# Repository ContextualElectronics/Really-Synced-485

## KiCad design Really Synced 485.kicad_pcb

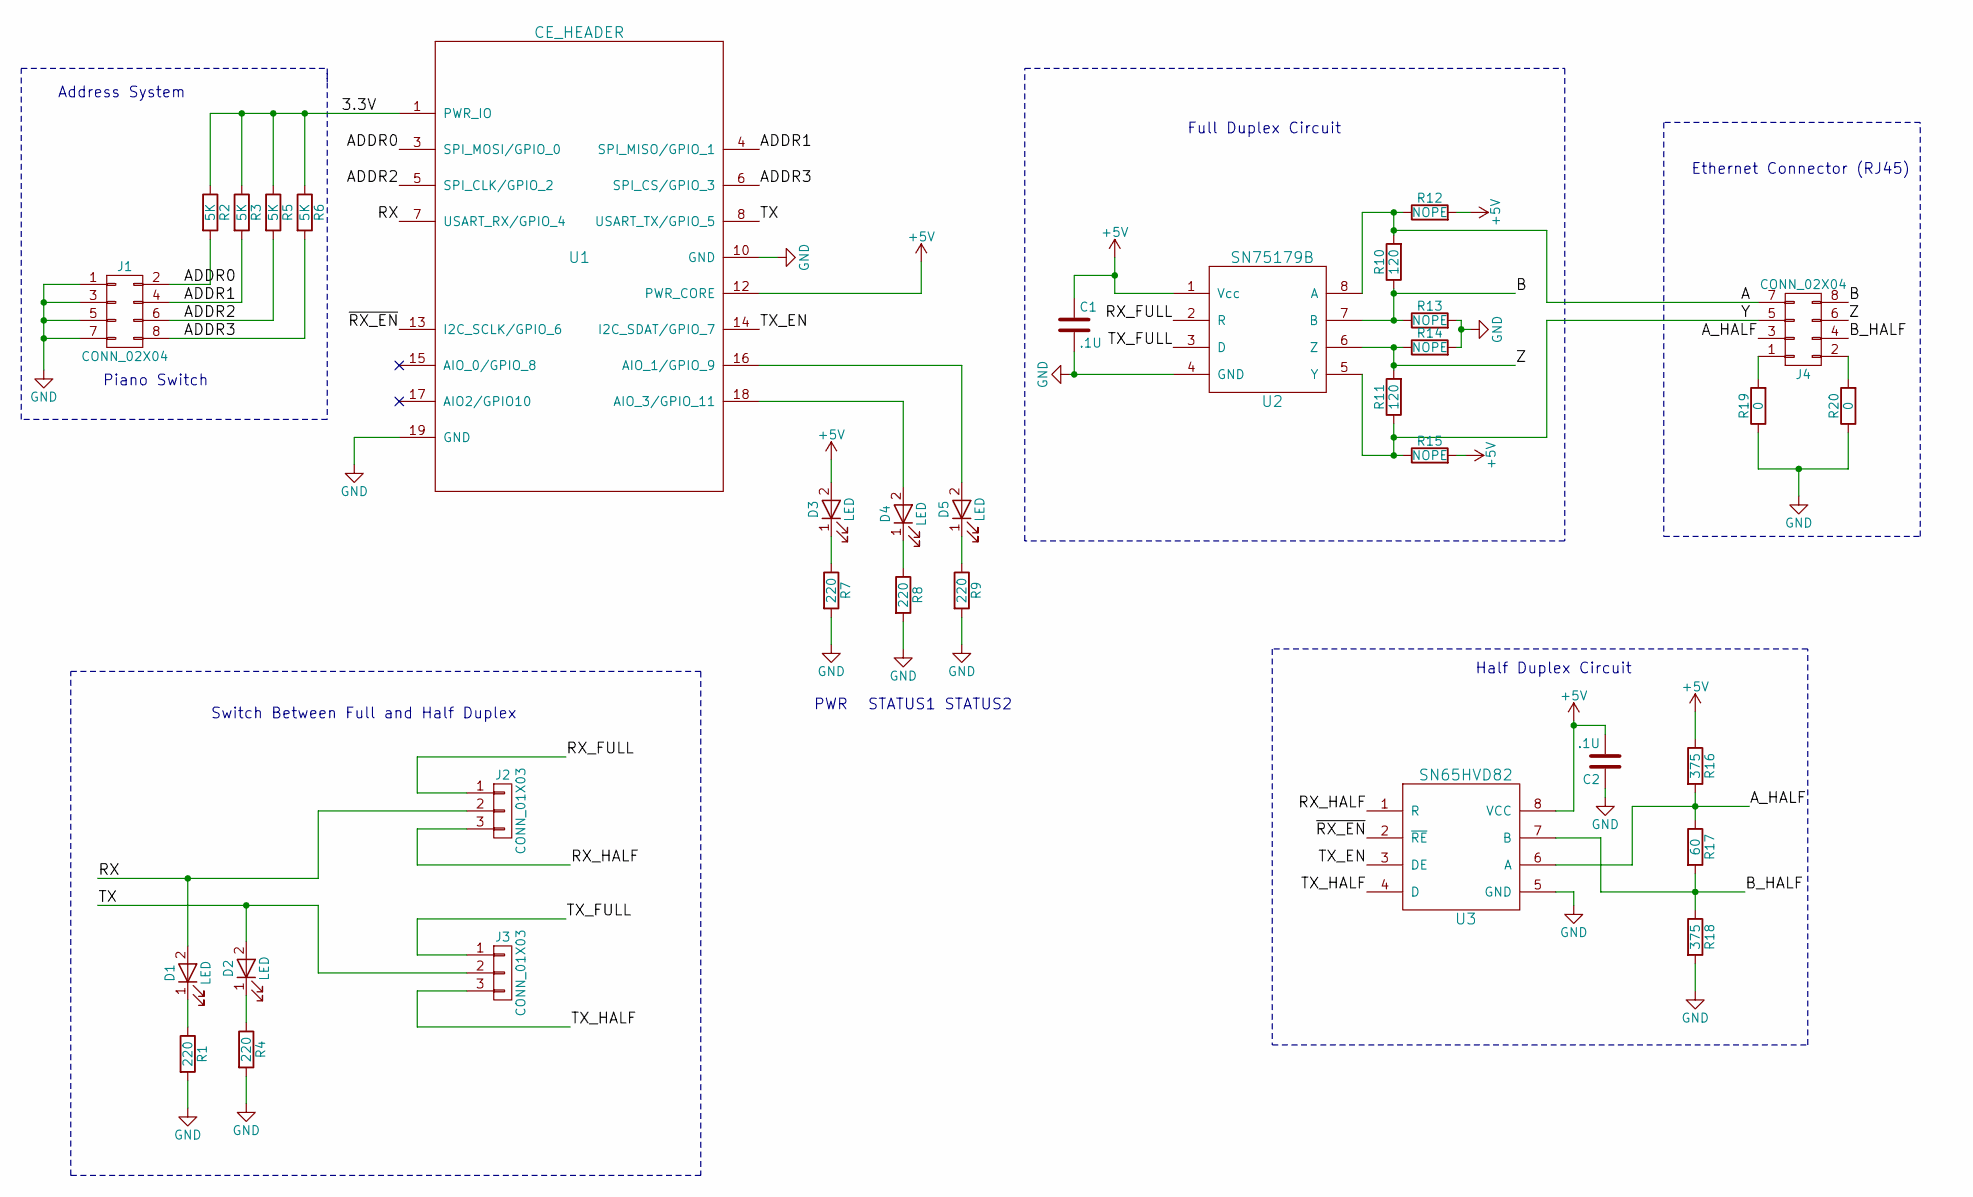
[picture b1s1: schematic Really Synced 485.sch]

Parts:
C1, C2: .1U; C_0805
D1, D2, D3, D4, D5: LED; LED_0805
J1: CONN_02X04; 195-4MST; MPN 195-4MST
J2, J3: CONN_01X03; Pin_Header_Straight_1x03_Pitch2.54mm
J4: CONN_02X04; 54602-908LF; MPN 54602-908LF
R1, R4, R7, R8, R9: 220; R_0805_HandSoldering
R2, R3, R5, R6: 5K; R_0805_HandSoldering
R10, R11: 120; R_0805_HandSoldering
R12, R13, R14, R15: NOPE; R_0805_HandSoldering
R16, R18: 375; R_0805_HandSoldering
R17: 60; R_0805_HandSoldering
R19, R20: 0; R_0805_HandSoldering
U1: CE_HEADER; CE_Header
U2: SN75179B; SOIC-8_3.9x4.9mm_Pitch1.27mm; MPN SN75179BDR
U3: SN65HVD82; SOIC-8_3.9x4.9mm_Pitch1.27mm

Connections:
+5V: C1.1, C2.2, D3.2 (A), R12.2, R15.2, R16.1, U1.12 (PWR_CORE), U2.1 (Vcc), U3.8 (VCC)
/3.3V: R2.1, R3.1, R5.1, R6.1, U1.1 (PWR_IO)
/A: J4.7, R10.2, R12.1, U2.8 (A)
/ADDR0: J1.2, R2.2, U1.3 (SPI_MOSI/GPIO_0)
/ADDR1: J1.4, R3.2, U1.4 (SPI_MISO/GPIO_1)
/ADDR2: J1.6, R5.2, U1.5 (SPI_CLK/GPIO_2)
/ADDR3: J1.8, R6.2, U1.6 (SPI_CS/GPIO_3)
/A_HALF: J4.3, R16.2, R17.1, U3.6 (A)
/B: J4.8, R10.1, R13.1, U2.7 (B)
/B_HALF: J4.4, R17.2, R18.1, U3.7 (B)
/RX: D1.2 (A), J2.2, U1.7 (USART_RX/GPIO_4)
/RX_FULL: J2.1, U2.2 (R)
/RX_HALF: J2.3, U3.1 (R)
/TX: D2.2 (A), J3.2, U1.8 (USART_TX/GPIO_5)
/TX_EN: U1.14 (I2C_SDAT/GPIO_7), U3.3 (DE)
/TX_FULL: J3.1, U2.3 (D)
/TX_HALF: J3.3, U3.4 (D)
/Y: J4.5, R11.1, R15.1, U2.5 (Y)
/Z: J4.6, R11.2, R14.1, U2.6 (Z)
/~RX_EN: U1.13 (I2C_SCLK/GPIO_6), U3.2 (~RE)
GND: C1.2, C2.1, J1.1, J1.3, J1.5, J1.7, R1.2, R4.2, R7.2, R8.2, R9.2, R13.2, R14.2, R18.2, R19.1, R20.1, U1.10 (GND), U1.19 (GND), U2.4 (GND), U3.5 (GND)
unnamed: D1.1 (K), R1.1
unnamed: D2.1 (K), R4.1
unnamed: D3.1 (K), R7.1
unnamed: D4.1 (K), R8.1
unnamed: D4.2 (A), U1.18 (AIO_3/GPIO_11)
unnamed: D5.1 (K), R9.1
unnamed: D5.2 (A), U1.16 (AIO_1/GPIO_9)
unnamed: J4.1, R19.2
unnamed: J4.2, R20.2

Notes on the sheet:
PWR
Address System
Switch Between Full and Half Duplex
Ethernet Connector (RJ45)
Full Duplex Circuit
Half Duplex Circuit
STATUS1
STATUS2
Piano Switch

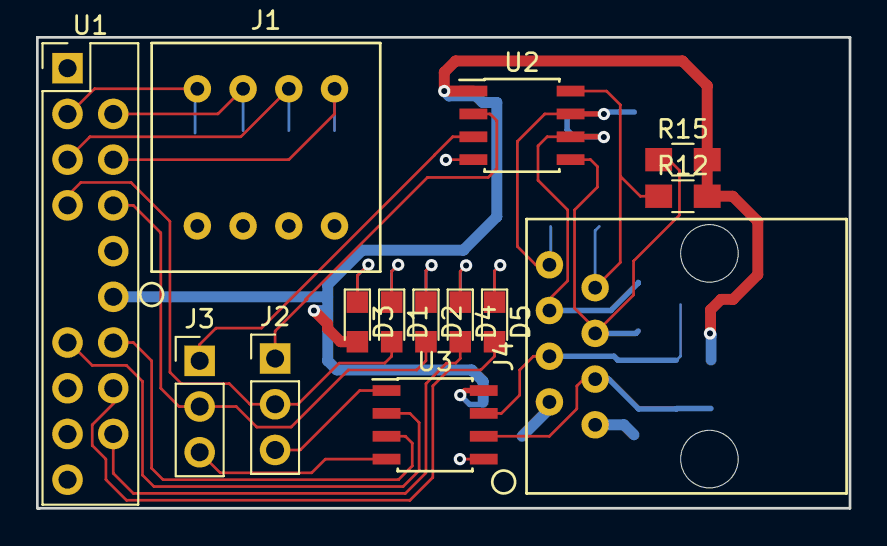
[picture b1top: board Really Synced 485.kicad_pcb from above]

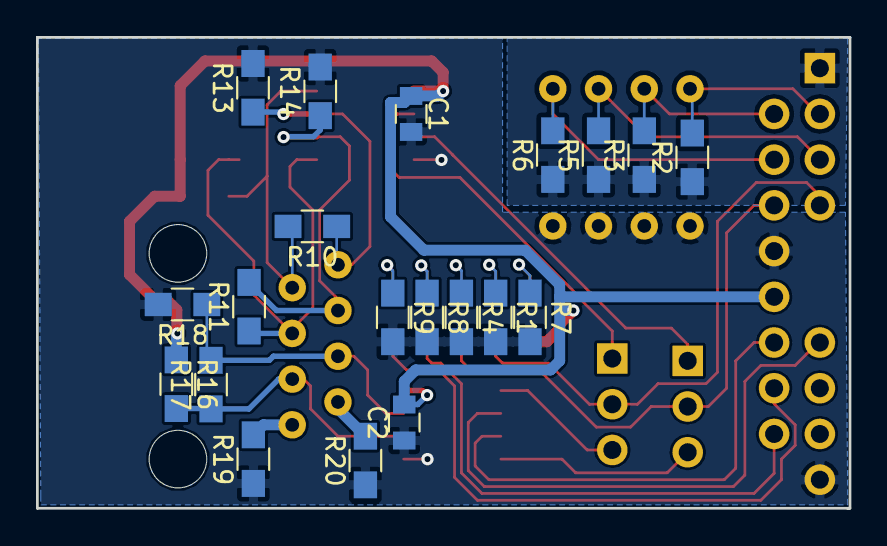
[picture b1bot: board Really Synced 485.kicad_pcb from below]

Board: 2 copper layers, 45.1 x 26.2 mm, 34 parts (20 on the bottom side), 30 nets.

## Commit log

2017-05-29 Added readme file
2017-05-29 Moved CE header library/footprint over
2017-05-29 Added resistors and driver component
2017-05-29 Finished schematic with piano switch and ethernet jack
2017-05-29 Added half duplex circuit and jumpers for switching between them
2017-05-29 Finished schematic
2017-05-29 Annotated schematic
2017-05-29 Mostly associated, need to make some footprints
2017-05-29 Renamed footprint repo
2017-05-29 Added footprint repo to project
2017-05-29 Created piano switch and ethernet footprints
2017-05-29 Created netlist
2017-05-29 Components imported, layout started
2017-05-29 Finished piano switch layout
2017-05-29 Added ground plane and 5V power routing
2017-05-29 LED placements done
2017-05-29 Finished initial layout, doing DRC next
2017-05-29 Finished layout with all silkscreen
2017-05-31 Updated MPN/link for half duplex driver
